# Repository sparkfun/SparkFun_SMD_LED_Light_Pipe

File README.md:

# SparkFun SMD LED Light Pipe

*SparkFun SMD LED Light Pipe rendered above an SMD Addressable LED  - [COM-25893](https://www.sparkfun.com/products/25893)*

The [SparkFun SMD LED Light Pipe](https://www.sparkfun.com/products/25893) is a 5mm plastic lens and housing for mounting SMD LEDs in a 90° board edge configuration. Commonly used for circuit board indicators (CBI). Circuit board indicators should be any color and take only one GPIO to control them all!

This repo houses the 3D files, [datasheet](<SparkFun SMD LED Light Pipe Datasheet.pdf>), as well as an example footprint and layout in KiCad.

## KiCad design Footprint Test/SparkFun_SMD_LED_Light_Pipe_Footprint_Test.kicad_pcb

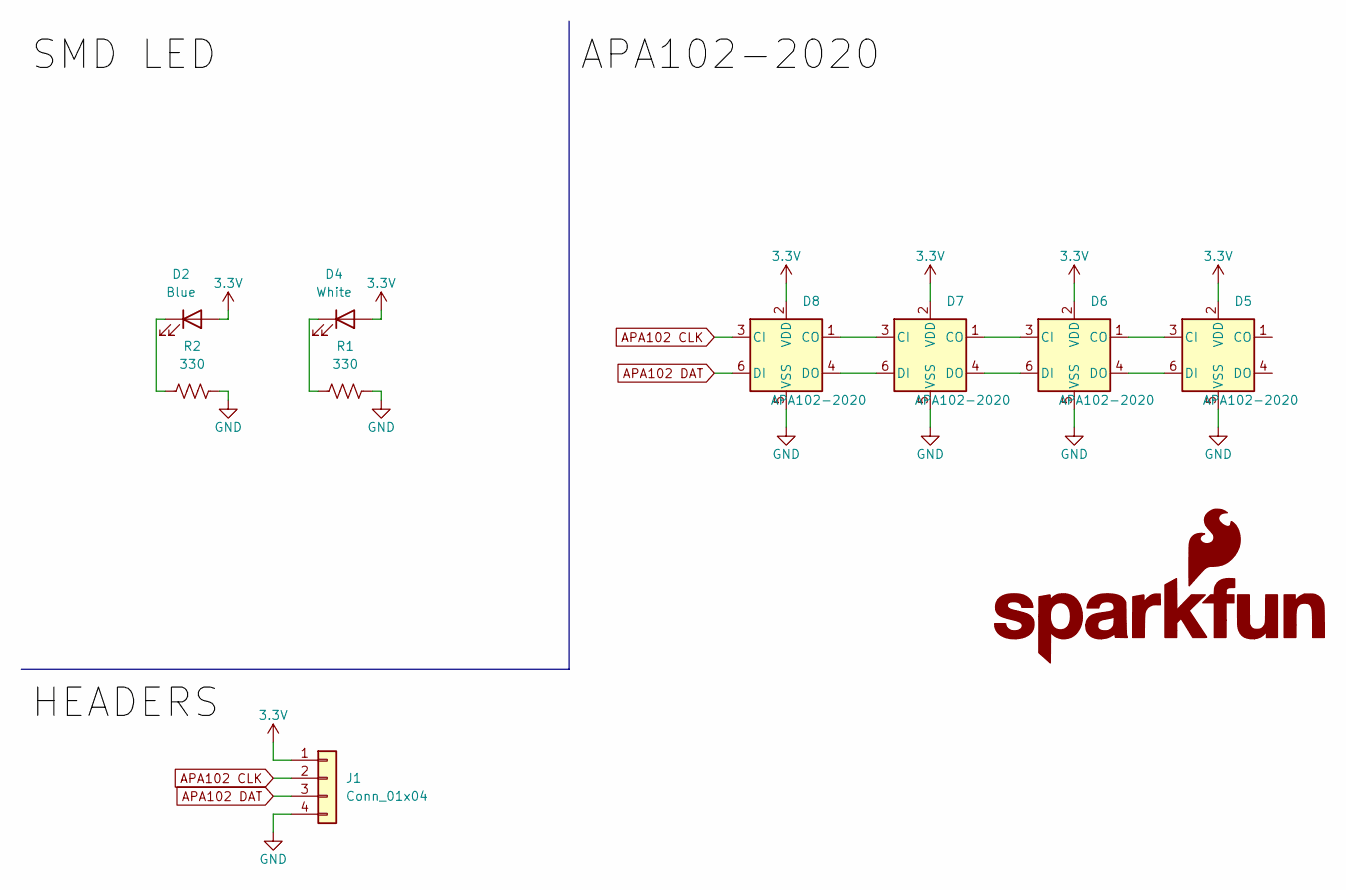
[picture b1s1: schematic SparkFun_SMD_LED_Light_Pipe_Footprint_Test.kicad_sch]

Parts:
D2: Blue; LED_0603_1608Metric_Blue
D4: White; LED_1206_3216Metric
D5, D6, D7, D8: APA102-2020; APA-102-2020
G1: SparkFun_Logo
J1: Conn_01x04; 1x04
R1, R2: 330; R_0603_1608Metric

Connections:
3.3V: D2.2 (A), D4.2 (A), D5.2 (VDD), D6.2 (VDD), D7.2 (VDD), D8.2 (VDD), J1.1
APA102 CLK: D8.3 (CI), J1.2
APA102 DAT: D8.6 (DI), J1.3
GND: D5.5 (VSS), D6.5 (VSS), D7.5 (VSS), D8.5 (VSS), J1.4, R1.1, R2.1
unnamed: D2.1 (K), R2.2
unnamed: D4.1 (K), R1.2
unnamed: D5.3 (CI), D6.1 (CO)
unnamed: D5.6 (DI), D6.4 (DO)
unnamed: D6.3 (CI), D7.1 (CO)
unnamed: D6.6 (DI), D7.4 (DO)
unnamed: D7.3 (CI), D8.1 (CO)
unnamed: D7.6 (DI), D8.4 (DO)

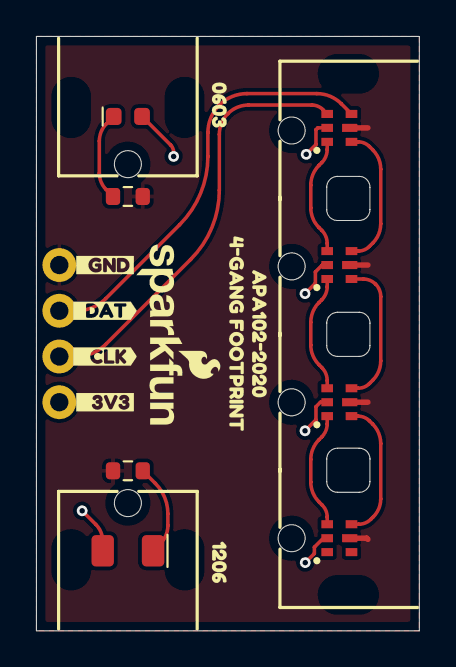
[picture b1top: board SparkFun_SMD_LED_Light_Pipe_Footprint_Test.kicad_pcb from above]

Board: 2 copper layers, 21.3 x 33.0 mm, 17 parts (0 on the bottom side), 12 nets.

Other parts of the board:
kibuzzard-668F3CFD: G***; kibuzzard-668F3CFD
kibuzzard-668F3D4E: G***; kibuzzard-668F3D4E
kibuzzard-668F3D18: G***; kibuzzard-668F3D18
kibuzzard-668F3D36: G***; kibuzzard-668F3D36
kibuzzard-668F3D73: G***; kibuzzard-668F3D73
kibuzzard-668F3D84: G***; kibuzzard-668F3D84
kibuzzard-668F3D94: G***; kibuzzard-668F3D94
kibuzzard-668F3DA2: G***; kibuzzard-668F3DA2

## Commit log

2024-07-11 Initial Commit
    Add files
2024-07-19 Add courtyard to footprints. Create external KiCad library.
2024-07-19 File rename
2024-07-19 Add keywords and datasheet link
2024-07-19 Update footprint name
2024-07-19 Fix top copper pour
2024-07-24 Update FP to use NPTH rather than edge cuts
2024-08-12 Update layout with 3D model
2024-08-14 Update examples
